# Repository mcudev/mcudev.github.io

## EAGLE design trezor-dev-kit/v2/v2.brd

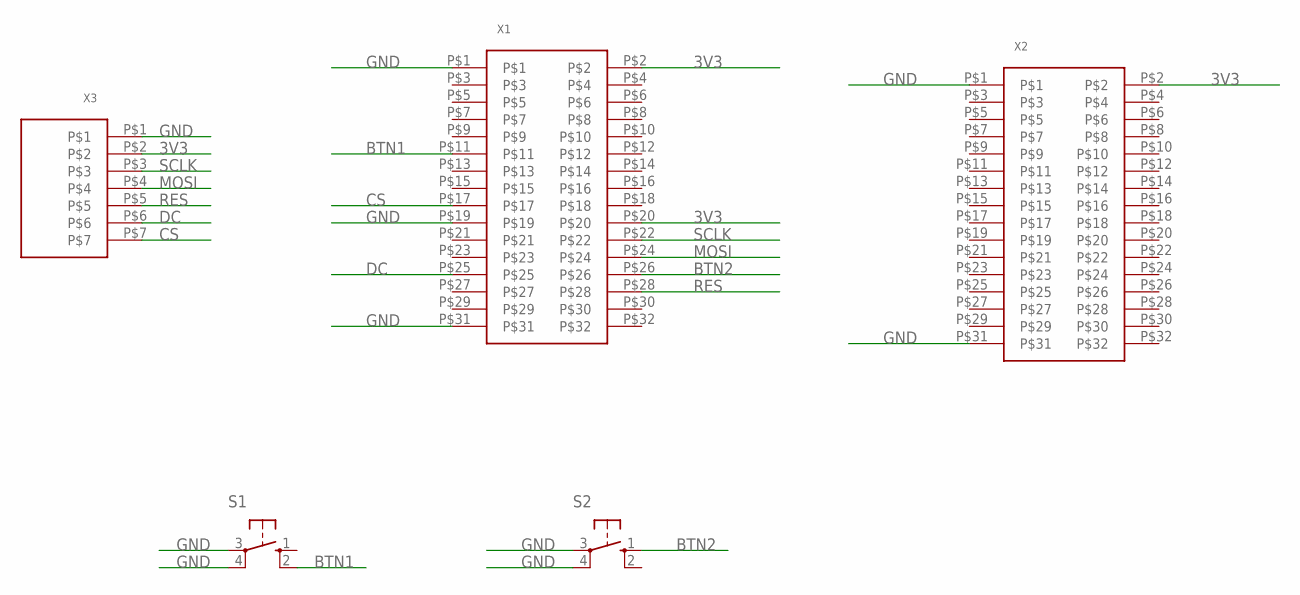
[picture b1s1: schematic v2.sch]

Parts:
S1: S1; B3F-40XX
S2: S2; B3F-40XX
X1, X2: 2X16-SOCKET-HEADER
X3: 1X7-SOCKET-HEADER

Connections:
3V3: X1.P$2, X1.P$20, X2.P$2, X3.P$2
BTN1: S1.2 (S1), X1.P$11
BTN2: S2.1 (S), X1.P$26
CS: X1.P$17, X3.P$7
DC: X1.P$25, X3.P$6
GND: S1.3, S1.4 (P1), S2.3, S2.4 (P1), X1.P$1, X1.P$19, X1.P$31, X2.P$1, X2.P$31, X3.P$1
MOSI: X1.P$24, X3.P$4
RES: X1.P$28, X3.P$5
SCLK: X1.P$22, X3.P$3

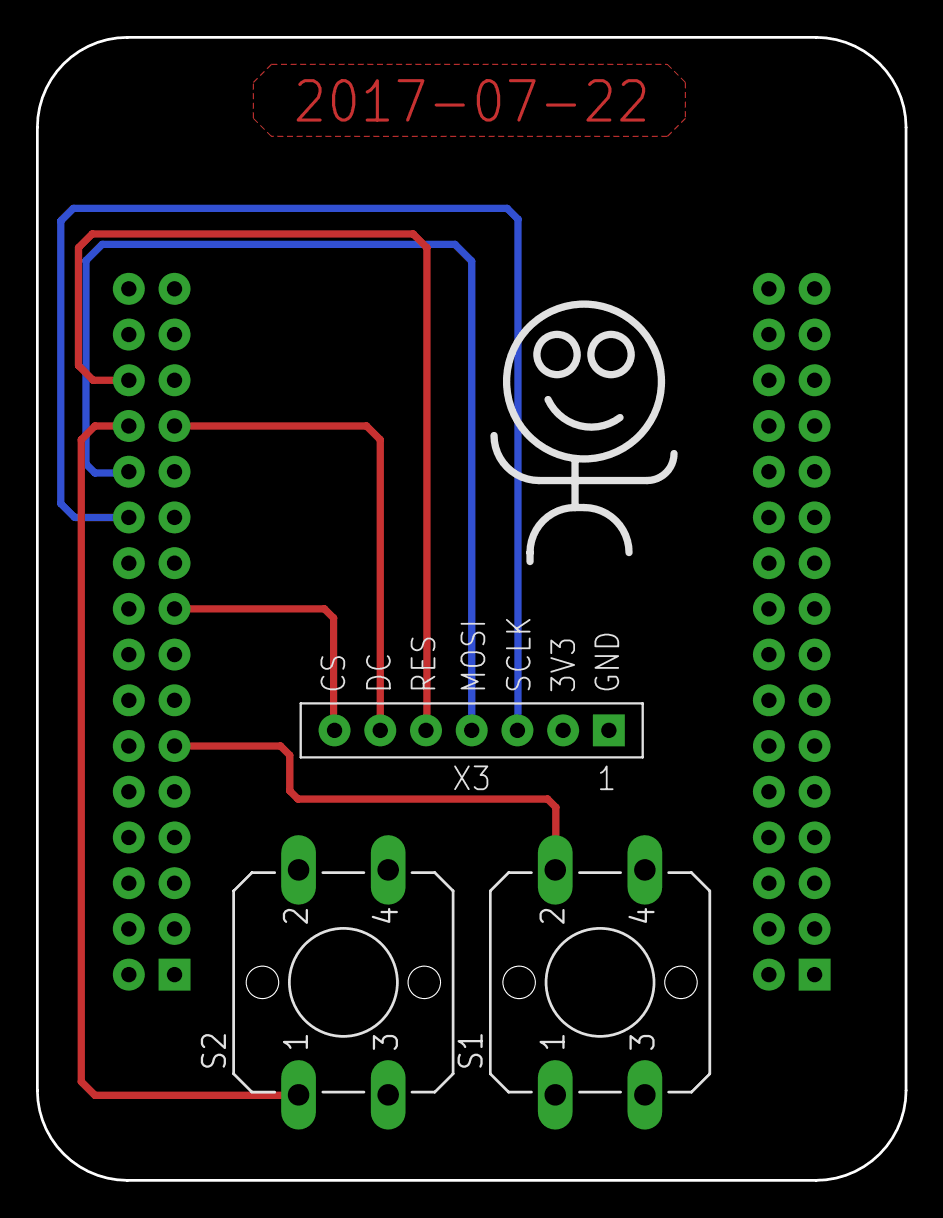
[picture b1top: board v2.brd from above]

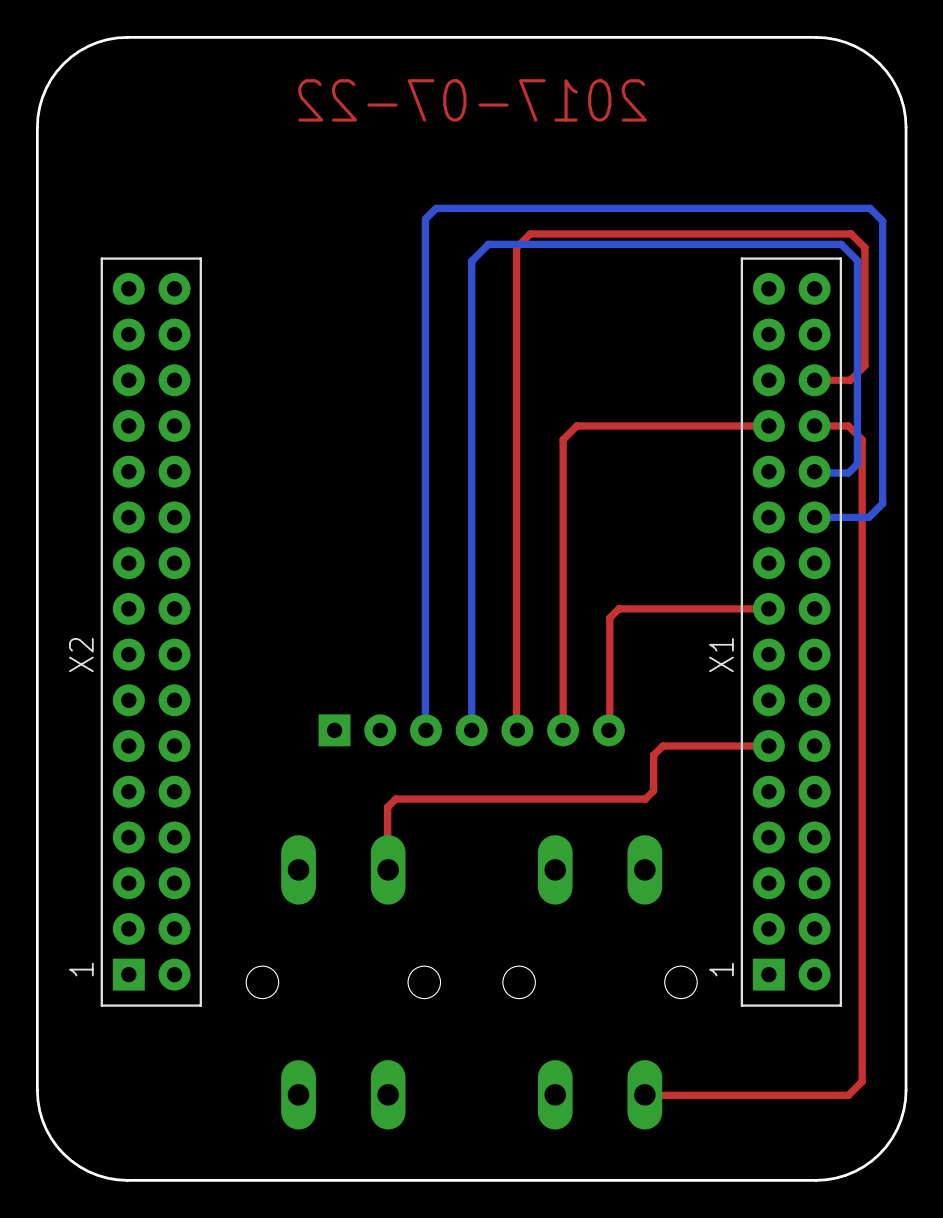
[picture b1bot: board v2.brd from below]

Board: 2 copper layers, 48.3 x 63.5 mm, 5 parts (2 on the bottom side), 9 nets.

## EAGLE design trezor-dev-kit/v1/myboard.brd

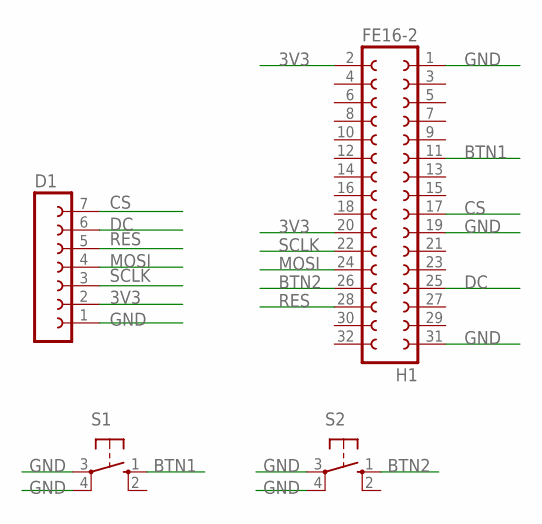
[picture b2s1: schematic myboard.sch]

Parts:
D1: FE07
H1: FE16-2
S1, S2: MY-B3F-40XX

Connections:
3V3: D1.2, H1.2, H1.20
BTN1: H1.11, S1.1 (S)
BTN2: H1.26, S2.1 (S)
CS: D1.7, H1.17
DC: D1.6, H1.25
GND: D1.1, H1.1, H1.19, H1.31, S1.3, S1.4 (P1), S2.3, S2.4 (P1)
MOSI: D1.4, H1.24
RES: D1.5, H1.28
SCLK: D1.3, H1.22

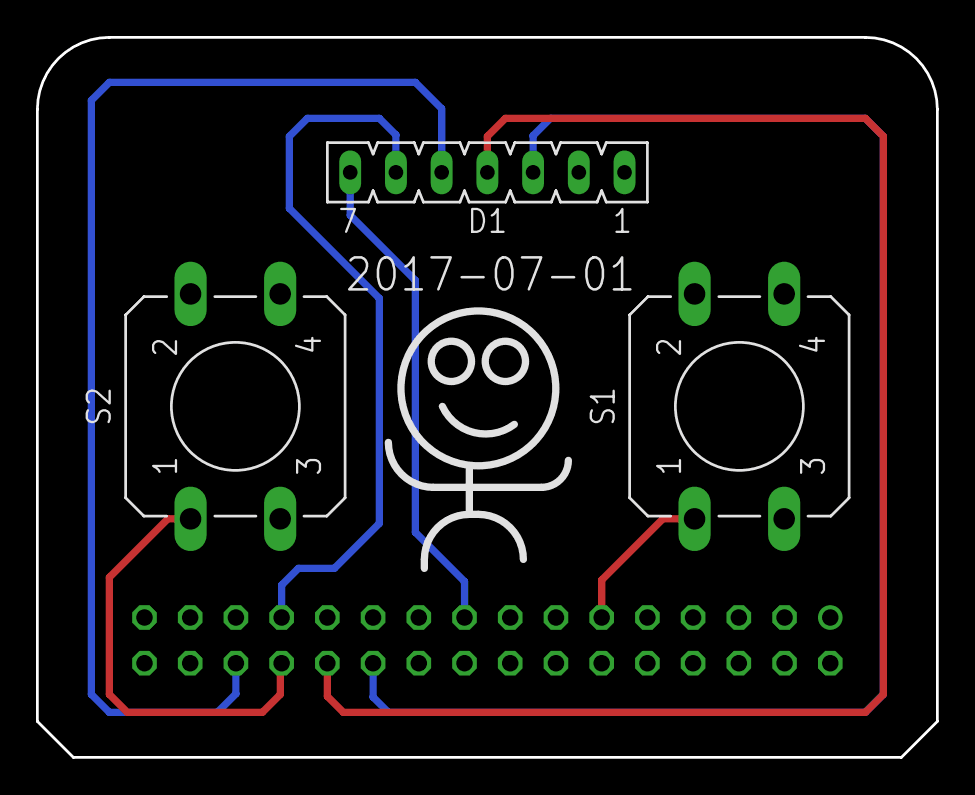
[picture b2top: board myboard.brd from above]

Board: 2 copper layers, 50.0 x 40.0 mm, 4 parts (1 on the bottom side), 9 nets.

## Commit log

2017-07-06 add html index
2017-07-09 video update
2017-07-18 pcb updates
2017-07-26 typo update
2017-08-01 add links
2017-08-29 udpates
2018-04-18 v1.6.1 related updates
2018-04-18 formatting update
2018-07-13 upgrade to ubuntu 18.04
2018-07-13 add info on upgrading st-link usb debug adapter firmware and add segwit examples
2018-07-16 add model t kit
2018-07-19 minor updates
2018-07-20 debug: add connect under reset instructions
2018-07-20 add line break
2018-07-20 add debug adapter firmware information
2018-07-24 explain dev board debugger to prototype board use
2018-08-04 runtime display identification related updates
2018-08-12 add low cost trezor one dev kit
2019-10-09 add notes about flash memory size and use of STM32F205RGT6
2019-11-13 tails 4 electrum configuration example
2019-11-13 add more tails electrum notes
2020-09-18 add instructions for using the trezor web wallet with tor browser on tails 4.10
2020-09-18 update iptables rule to consider conntrack state too
2020-09-22 tails 4.11 updates
2020-09-22 more tails 4.11 updates
